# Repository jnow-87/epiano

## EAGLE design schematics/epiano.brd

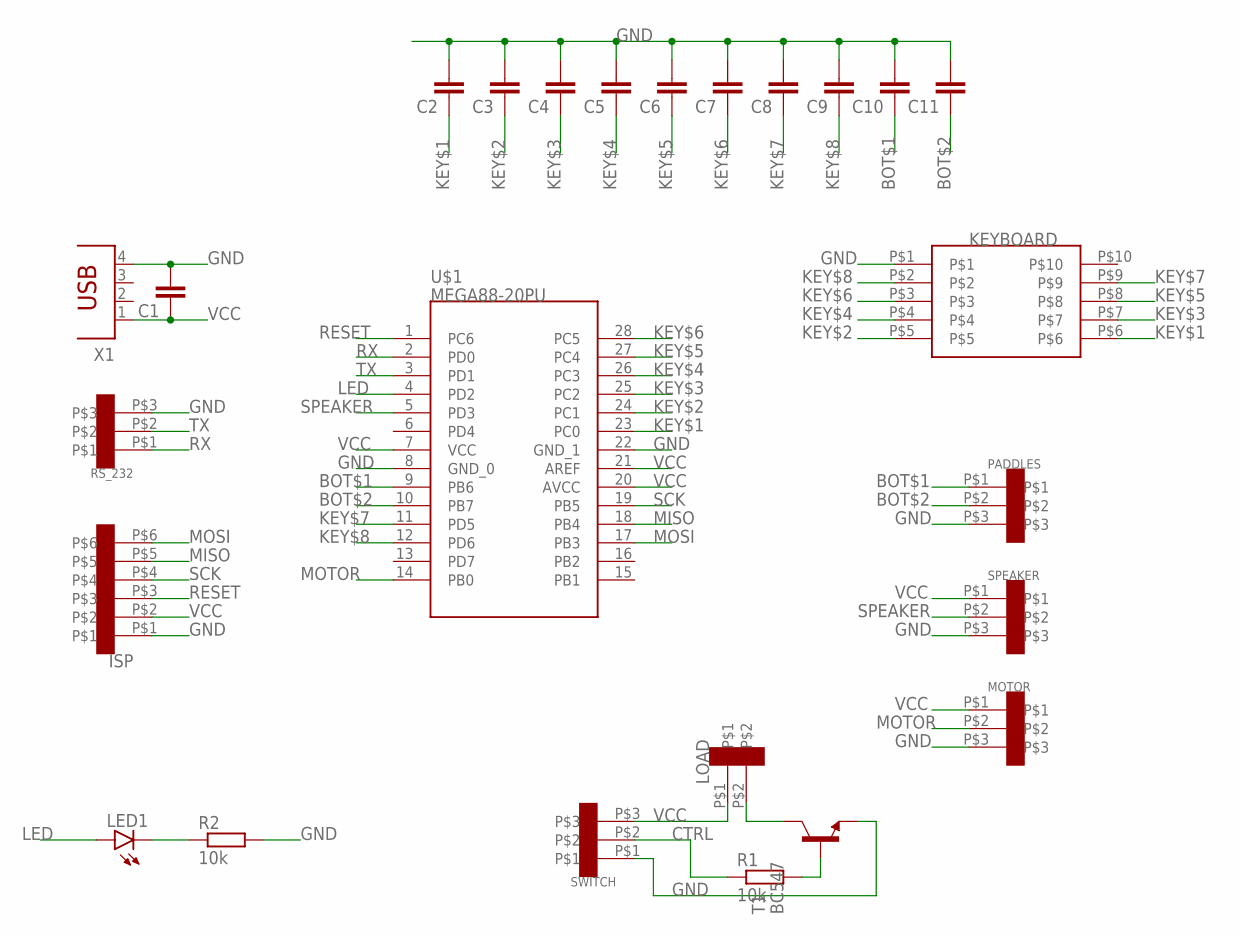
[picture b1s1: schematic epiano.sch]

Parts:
C1: C-EU025-060X050; C025-060X050
C2, C3, C4, C5, C6, C7, C8, C9, C10, C11: C-EU025-024X044; C025-024X044
ISP: CON_DIL_6
KEYBOARD: CON_DIL_2X5
LED1: LED3MM
LOAD: CON_DIL_2
MOTOR: CON_DIL_3
PADDLES: CON_DIL_3
R1: 10k; 0204/5
R2: 10k; 0207/15
RS_232: CON_DIL_3
SPEAKER: CON_DIL_3
SWITCH: CON_DIL_3
T1: BC547; TO92
U$1: MEGA88-20PU; DIL28-3
X1: PN87520

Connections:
BOT$1: C10.1, PADDLES.P$1, U$1.9 (PB6)
BOT$2: C11.1, PADDLES.P$2, U$1.10 (PB7)
CTRL: R1.1, SWITCH.P$2
GND: C1.2, C2.2, C3.2, C4.2, C5.2, C6.2, C7.2, C8.2, C9.2, C10.2, C11.2, ISP.P$1, KEYBOARD.P$1, MOTOR.P$3, PADDLES.P$3, R2.2, RS_232.P$3, SPEAKER.P$3, SWITCH.P$1, T1.1 (E), U$1.8 (GND_0), U$1.22 (GND_1), X1.4
KEY$1: C2.1, KEYBOARD.P$6, U$1.23 (PC0)
KEY$2: C3.1, KEYBOARD.P$5, U$1.24 (PC1)
KEY$3: C4.1, KEYBOARD.P$7, U$1.25 (PC2)
KEY$4: C5.1, KEYBOARD.P$4, U$1.26 (PC3)
KEY$5: C6.1, KEYBOARD.P$8, U$1.27 (PC4)
KEY$6: C7.1, KEYBOARD.P$3, U$1.28 (PC5)
KEY$7: C8.1, KEYBOARD.P$9, U$1.11 (PD5)
KEY$8: C9.1, KEYBOARD.P$2, U$1.12 (PD6)
LED: LED1.A, U$1.4 (PD2)
MISO: ISP.P$5, U$1.18 (PB4)
MOSI: ISP.P$6, U$1.17 (PB3)
MOTOR: MOTOR.P$2, U$1.14 (PB0)
unnamed: R1.2, T1.2 (B)
unnamed: LOAD.P$2, T1.3 (C)
unnamed: LED1.K (C), R2.1
RESET: ISP.P$3, U$1.1 (PC6)
RX: RS_232.P$1, U$1.2 (PD0)
SCK: ISP.P$4, U$1.19 (PB5)
SPEAKER: SPEAKER.P$2, U$1.5 (PD3)
TX: RS_232.P$2, U$1.3 (PD1)
VCC: C1.1, ISP.P$2, LOAD.P$1, MOTOR.P$1, SPEAKER.P$1, SWITCH.P$3, U$1.7 (VCC), U$1.20 (AVCC), U$1.21 (AREF), X1.1

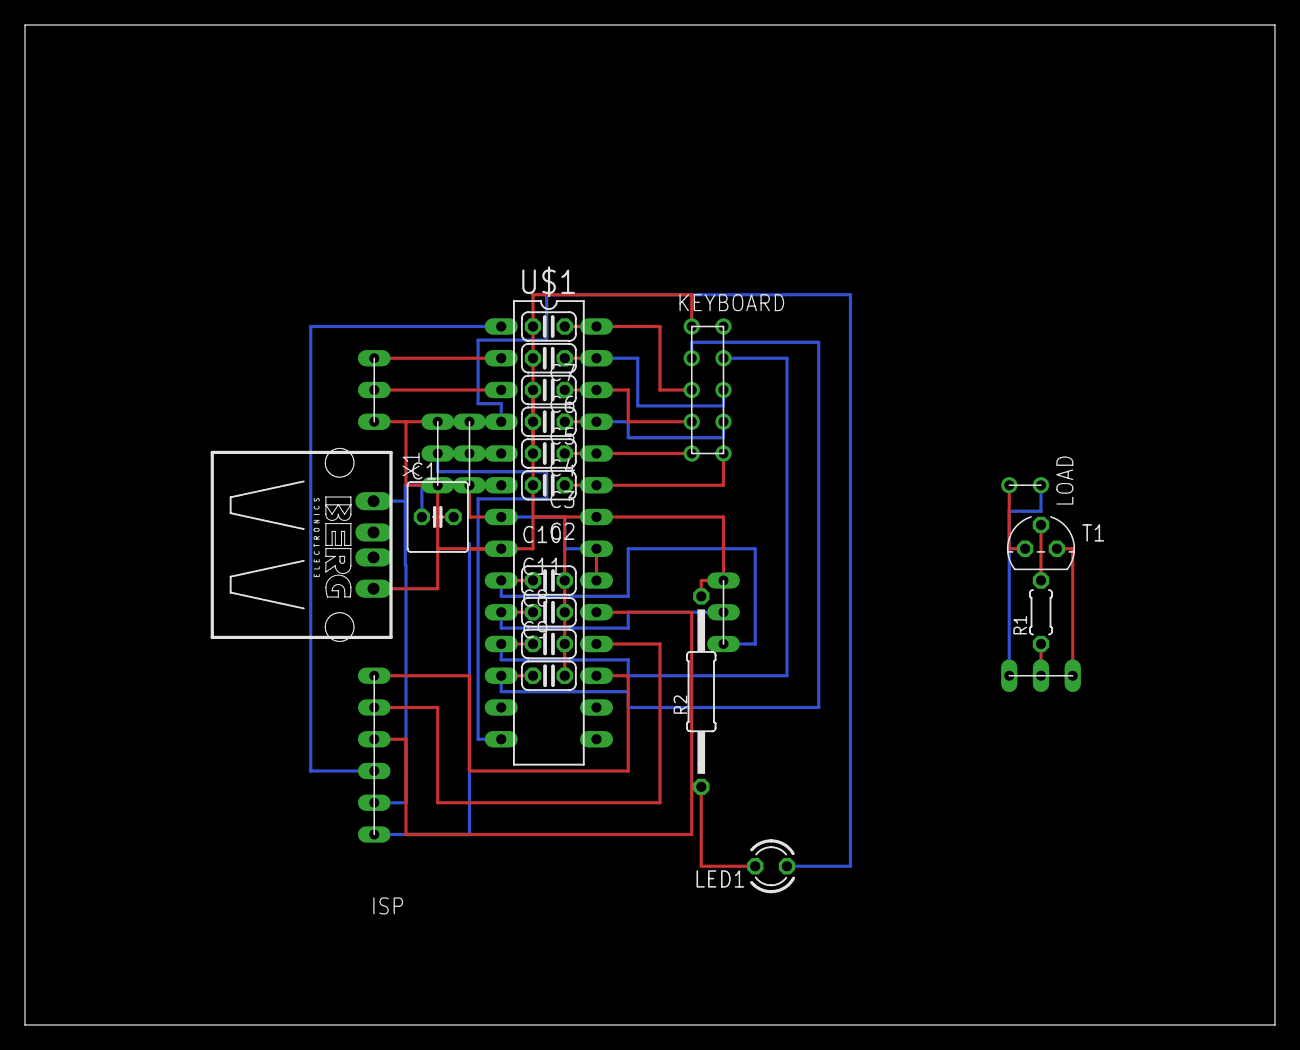
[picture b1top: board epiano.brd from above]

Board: 2 copper layers, 100.0 x 80.0 mm, 25 parts (0 on the bottom side), 25 nets.

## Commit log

2021-12-21 [initial]
2021-12-21 Squashed 'scripts/build/' content from commit 466a21a
    git-subtree-dir: scripts/build
    git-subtree-split: 466a21abf5555f839ca33efdd55aa48ac78e82b8
2021-12-21 Squashed '.githooks/' content from commit f2384fe
    git-subtree-dir: .githooks
    git-subtree-split: f2384fecb911fc3888e3a2d4a06c16e7cbc74db3
2021-12-21 [schematics]
    Add schematics for the epiano main, speaker and motor board.
2022-01-16 [build config and drivers]
    Add makefiles, project config and drivers for uart and mcu
    initialisation.
2022-01-16 [actuator drivers]
    Add drivers for the status led, speaker and motor.
2022-01-16 [mcu pin control]
    - add atmega pin control functions
    - add atmega88 pin configuration
2022-01-16 [task]
    Add support for timer-based tasks.
2022-01-16 [main]
    Add keyboard handling and respective actuator control.
2022-01-16 [secret]
    Add support for a secret key combination.
2023-05-26 Squashed 'scripts/build/' changes from 466a21a..2d6dcbc
    2d6dcbc [buildsys: (un)install helper]
    0a5ad38 [buildsys: fix lex, yacc, gperf header rules]
    ed9e848 [buildsys: fix gperf header generation rules]
    0f7e750 [buildsys: fix versionheader rebuild]
    0ec035d [buildsys: introduce terminal escape codes]
    2de09bc [test coverage: fix coverage for unit tests]
